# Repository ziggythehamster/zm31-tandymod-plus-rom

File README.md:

ZM31 TandyMod+ ROM Version
==========================

This repo contains everything needed to perform [Alan Hightower's TandyMod+](https://www.retrotronics.org/svn/jride/trunk/tandymod/) using more commonly programmable ROMs rather than GAL chips. If you have a GAL programmer, his board is much more compact (it's SMT) and less likely to run into issues due to ROMs being slow/degraded.

The general concept is that rather than implement this simple logic on a GAL chip or several traditional logic chips, I'm implementing this 8-input logic function using a ROM. Think about the address select lines as logic inputs and the data output lines as logic outputs. If this were working as an 8-way OR gate with two outputs, then address 0 (all address lines low) would have the value 0b00, and all of the 255 other possible addresses would have the value 0b11. 256-bit modern-ish ROMs, however, are uncommon. So how do we handle larger ROMs? If you repeat these 256 values over and over again until you hit the end of the ROM, then A8 and greater can be either 0 or 1 and the logic table still works. This works out very nicely because some ROMs have their +5V input as the last pin, and on bigger ROMs, that pin is an address pin. [This is a handy table of how the pins match up between the different sized chips](http://www.z80.info/gfx/eprom.gif).

What the Mod Does
-----------------

It's well known that the Tandy 1000 is a clone of the IBM PCjr. While cloning the PCjr, Tandy fixed a number of silly bugs that IBM left in (probably to make the PCjr incompatible with the IBM PC). One of those bugs is how the video memory is used. I don't completely understand the bug, so this explanation may be a bit inaccurate, but when in 320x200 16-color mode, you can only access the first 16KB of video memory at BC000 (B8000 is just a repeat of BC000) even though there is at least 32KB of video memory. There is some other way to access the other half of the 32KB video memory, which PCjr applications have to use, but this makes programming much more difficult. On the Tandy 1000, BC000 to BFFFF is accessible as a contiguous 32KB chunk. This mod fixes this. The end result is that Tandy 1000 applications that normally have a Venetian blinds defect (black bars every inch or so) will now display correctly. There are only a handful of PCjr applications which don't work with this mod enabled, which is why there is a toggle jumper.

Performing the Mod
------------------

1. Check that you have the parts you need. You will need the mod board, a 2.54mm jumper, 2.54mm header pins, a programmed ROM, a low-profile small DIP16 socket, and a low-profile DIP28 socket.
2. Test that Turbo Outrun starts with Venetian blinds in Tandy 16-color mode.
3. Build the board.
4. Desolder ZM31, a 74LS157 under the floppy drive. Locate the chip by referencing [page B-19 of the PCjr technical reference](https://archive.org/details/bitsavers_ibmpcpcjrPceNov83_24513363/page/n515).
5. Install the low-profile DIP16 socket in place of the 74LS157. Install the 74LS157 in this socket.
6. Test that Turbo Outrun still starts with Venetian blinds in Tandy 16-color mode.
7. Remove the 74LS157 again, and insert the mod board.
8. Set the jumper to Tandy Mode On.
9. Test that Turbo Outrun starts _without_ Venetian blinds in Tandy 16-color mode.
10. Set the jumper to Tandy Mode Off.
11. Test that Turbo Outrun starts _with_ Venetian blinds in Tandy 16-color mode.
12. Put the jumper back to Tandy Mode On.

Errata
------

None at the moment.

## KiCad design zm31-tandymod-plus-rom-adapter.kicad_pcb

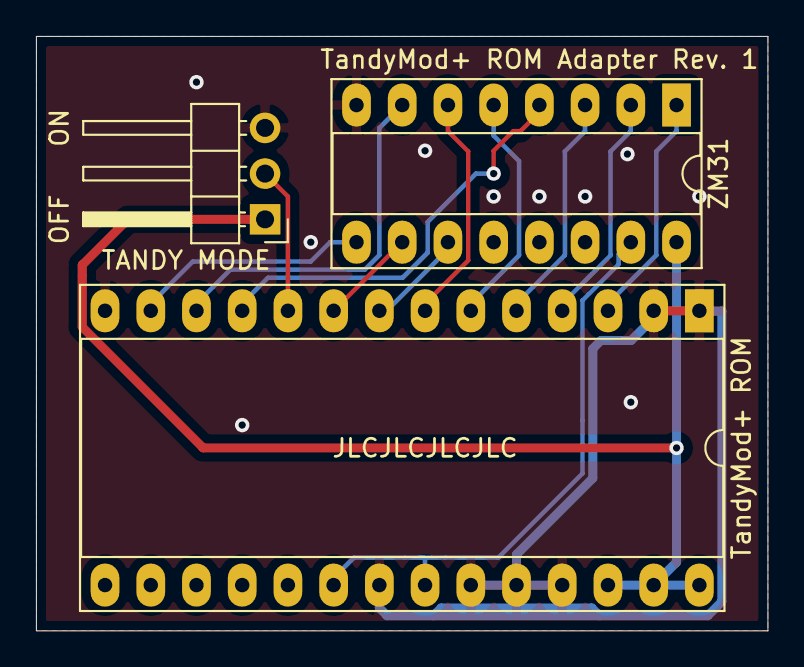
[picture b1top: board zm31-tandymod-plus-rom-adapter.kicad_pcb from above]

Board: 2 copper layers, 40.6 x 33.0 mm, 3 parts (0 on the bottom side), 14 nets.

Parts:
TANDY MODE: SW_DPDT_x2; PinHeader_1x03_P2.54mm_Horizontal
TandyMod+ ROM: ROM Socket; DIP-28_W15.24mm_Socket_LongPads
ZM31: ZM31 Socket; DIP-16_W7.62mm_Socket_LongPads

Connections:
/GND: TANDY MODE.3, TandyMod+ ROM.1, TandyMod+ ROM.2, TandyMod+ ROM.14, TandyMod+ ROM.21, TandyMod+ ROM.23, TandyMod+ ROM.24, TandyMod+ ROM.25, ZM31.8
/OUT14: TandyMod+ ROM.11, ZM31.4
/OUT15: TandyMod+ ROM.12, ZM31.7
/OUT16: TandyMod+ ROM.13, ZM31.9
/PG0: TandyMod+ ROM.4, ZM31.2
/PG1: TandyMod+ ROM.6, ZM31.5
/PG2: TandyMod+ ROM.8, ZM31.11
/SEL: TandyMod+ ROM.3, ZM31.1
/VCC: TANDY MODE.1, TandyMod+ ROM.26, TandyMod+ ROM.27, TandyMod+ ROM.28, ZM31.16
/XA14: TandyMod+ ROM.5, ZM31.3
/XA15: TandyMod+ ROM.7, ZM31.6
/XA16: TandyMod+ ROM.9, ZM31.10
/~ENABLE: TandyMod+ ROM.20, TandyMod+ ROM.22, ZM31.15
/~TANDY: TANDY MODE.2, TandyMod+ ROM.10

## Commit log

2019-10-26 Add dotfiles
2019-10-26 Add README
2019-10-26 Add ROM generator and generated ROMs
2019-10-26 Add KiCad files
2019-10-26 Add license from upstream as this is a derivative work
2019-10-26 Label the nets
2019-10-26 Add a PDF schematic
2019-10-26 Update with the named nets
2019-10-26 Not sure why the project file updated but it did
